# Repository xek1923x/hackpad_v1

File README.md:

# xek1923x: Hackpad v1
My very first own hackpad! Totally excited to build it together and use it!

## Features:
- 6 keys, 4 of them are arrow keys, the others are customizable keys
- Rotary encoder -> used for volume control!

## PCB
Designing the PCB was easier than expected. I should say that the guide was incredibly well-designed and helped me to get an overall impression of KiCAD.

### Schematic design:

### PCB design:

## CAD
Thankfully, Autodesk Fusion is FREE for students :). For the CAD, again, I believe that the guide helped me to figure out how to use the software.

### These are the single elements:

### That's how it'll look like:

## BOM
- 1x XIAO-RP2040-DIP
- 1x EC11 Rotary encoder
- 6x MX-Style switches
  - obviously: 6x Blank DSA keycaps
- 2x SK6812 MINI-E LEDs

## notes
That's it! I had a lot of fun in completing the project and will definitely use my hackpad from now on!

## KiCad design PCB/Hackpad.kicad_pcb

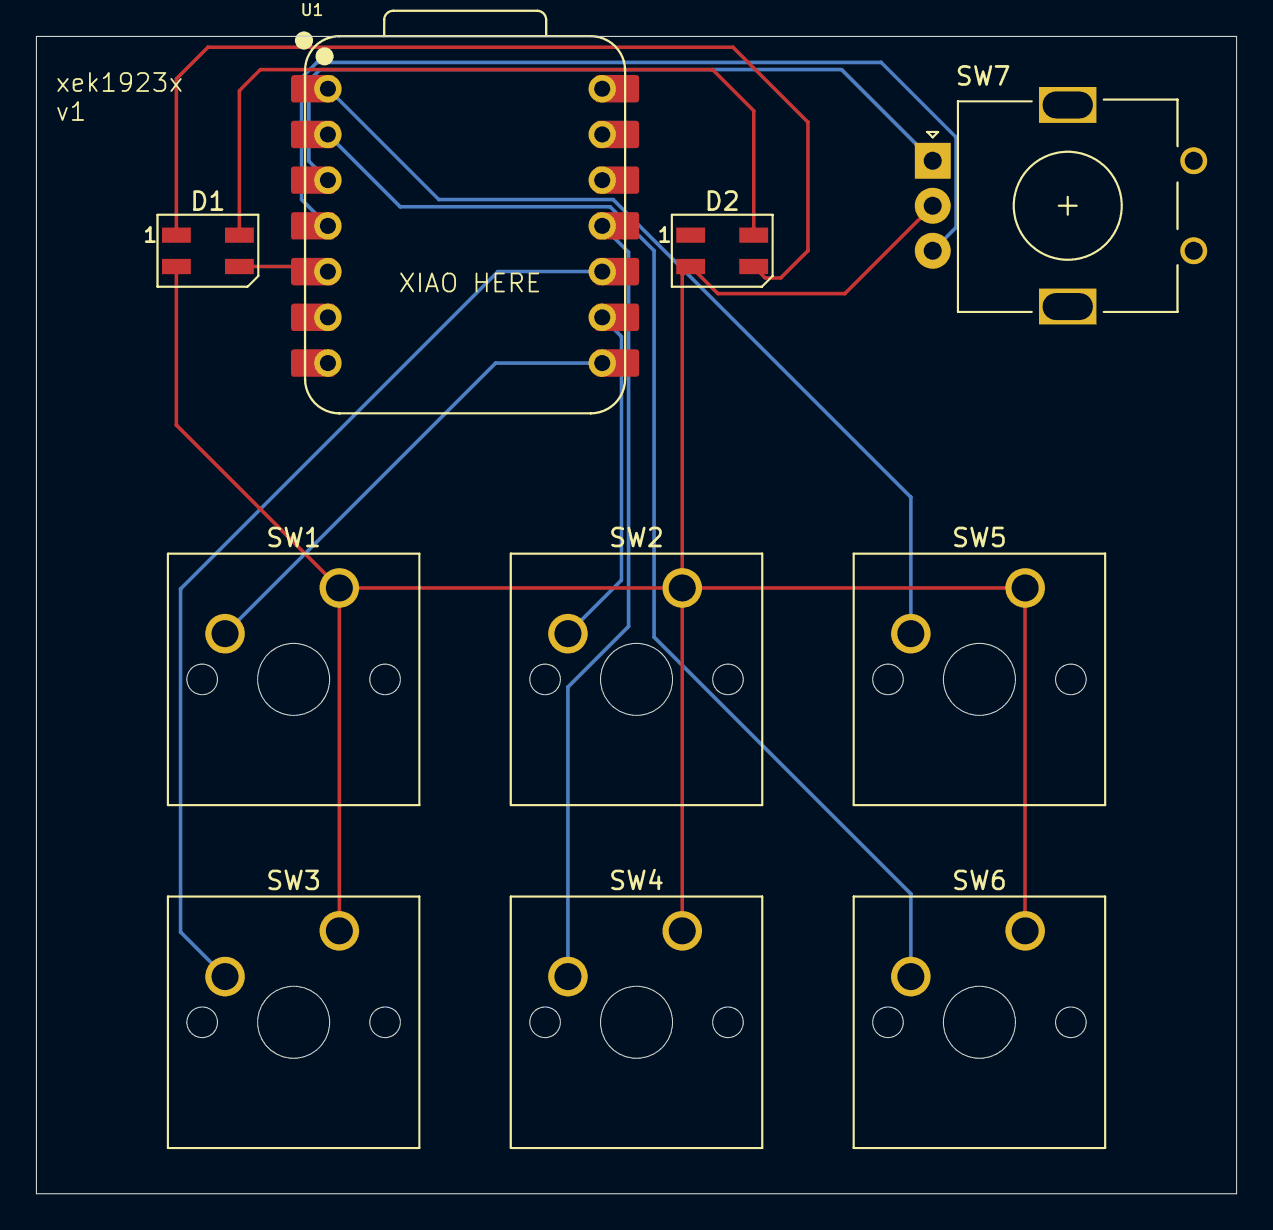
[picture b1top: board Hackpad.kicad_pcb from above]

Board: 2 copper layers, 66.7 x 64.3 mm, 10 parts (0 on the bottom side), 12 nets.

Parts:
D1, D2: SK6812MINI; LED_SK6812MINI_PLCC4_3.5x3.5mm_P1.75mm
SW1, SW2, SW3, SW4, SW5, SW6: SW_Push; SW_Cherry_MX_1.00u_PCB
SW7: RotaryEncoder; RotaryEncoder_Alps_EC11E_Vertical_H20mm
U1: XIAO-RP2040-DIP

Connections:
+5V: D1.4 (VDD), D2.4 (VDD)
GND: D1.2 (VSS), D2.2 (VSS), SW1.1, SW2.1, SW3.1, SW4.1, SW5.1, SW6.1, SW7.C
unnamed: D1.3 (DIN), U1.5 (GPIO6/SDA)
unnamed: D1.1 (DOUT), D2.3 (DIN)
unnamed: SW1.2, U1.8 (GPIO1/RX)
unnamed: SW2.2, U1.9 (GPIO2/SCK)
unnamed: SW4.2, U1.11 (GPIO3/MOSI)
unnamed: SW3.2, U1.10 (GPIO4/MISO)
unnamed: SW5.2, U1.1 (GPIO26/ADC0/A0)
unnamed: SW6.2, U1.2 (GPIO27/ADC1/A1)
unnamed: SW7.A, U1.3 (GPIO28/ADC2/A2)
unnamed: SW7.B, U1.4 (GPIO29/ADC3/A3)

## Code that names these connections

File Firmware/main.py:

import board
from kmk.kmk_keyboard import KMKKeyboard
from kmk.scanners.keypad import KeysScanner
from kmk.keys import KC
from kmk.modules.macros import Macros, Press, Release, Tap
from kmk.modules.encoder import EncoderHandler
from kmk.extensions.media_keys import MediaKeys

keyboard.extensions.append(MediaKeys())

keyboard = KMKKeyboard()
macros = Macros()
keyboard.modules.append(macros)

encoders = EncoderHandler()
keyboard.modules.append(encoders)

# Define your button pins here (based on the schematic: SW1 to SW6
KEY_PINS = [
    board.GPIO1,  # SW1
    board.GPIO2,  # SW2
    board.GPIO4,  # SW3
    board.GPIO3,  # SW4
    board.GPIO26,   # SW5
    board.GPIO27,   # SW6
    board.GPIO29,   # SW7 left (rotary)
    board.GPIO28,   # SW7 right (rotary)
]

keyboard.matrix = KeysScanner(
    pins=KEY_PINS,
    value_when_pressed=False,
)

# Define the rotary encoder pins (A, B, and no integrated button pin since push is separate)
encoders.pins = [
    (board.GPIO29, board.GPIO28, None),
]

# Example keymap for the 7 buttons
keyboard.keymap = [
    [
        # Currently, SW1 and SW5: i haven't assigned anything on purpose!
        KC.NO, KC.UP, KC.LEFT, KC.DOWN, KC.NO, KC.RIGHT, KC.VOLD, KC.VOLU, 
    ]
]

# Example encoder map (one layer, one encoder: clockwise, counterclockwise, button - but button is handled separately)
encoders.map = [
    [(KC.VOLU, KC.VOLD, KC.NO)],  # Use KC.NO for button since it's in the keymap
]

if __name__ == '__main__':
    keyboard.go()

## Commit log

2025-12-25 Add readme
2025-12-26 Create README.md for Hackpad v1 project
    Added initial README.md with project details and features.
2025-12-26 Add encoder and media keys support to main.py
    Refactor keyboard setup to include encoder and media keys.
